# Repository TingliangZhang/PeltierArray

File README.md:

# PeltierArray
帕尔贴阵列 PCB and design

## 选型

MCU: Mega 2560 PRO (Embed) CH340G/ATmega2560-16AU

https://robotdyn.com/mega-2560-pro-embed-ch340g-atmega2560-16au.html

MOS管

[MOS(场效应管)/KIA50N03BD](https://item.szlcsc.com/458575.html)

接口

JST丨常用系列和型号选型推荐大全

https://www.szlcsc.com/info/13106.html

> 一开始选择 **PH系列 插座 1\*4P 间距2mm 卧插** B4B-PH-SM4-TB(LF)
>

后更改方案为

帕尔贴接口为PH2.0x2

PH-2A 2P 脚距2.0mm 直插

https://item.szlcsc.com/2693.html

温度传感器接口保持原来的

XH插座 1*2P 直针 间距2.5mm

https://item.szlcsc.com/169360.html

电源接口

> DC头：**DC连接器 DC-002-2.0A-1.3 DC插座 W11.4XD5.0XH7.4,内芯1.3,2A 12V**
>
> https://item.szlcsc.com/353351.html
>
> 可能要稍稍掰弯

更改为[AC/DC电源插座/DC-005 5.5-2.0MM 铁材质](https://item.szlcsc.com/16896.html)

发光二极管

LED灯绿_Iv=112-285_λd=520-535 二极管_发光二极管

SMT

或手贴

翠绿LED

https://item.szlcsc.com/207066.html

电容

[贴片电容/47uF(476) ±20% 25V](https://item.szlcsc.com/389810.html)

[引线型铝电解电容/47uF 50V黑高频](https://item.szlcsc.com/46672.html)

[贴片电容/10uF(106) ±20% 25V](https://item.szlcsc.com/97651.html)

其他

[肖特基二极管/SS14](https://item.szlcsc.com/2857.html)

[发光二极管/翠绿LED](https://item.szlcsc.com/207066.html)

半桥驱动

参考 [**wavgat**](https://wavgat.tmall.com/) 的MOS管驱动模块

https://detail.tmall.com/item.htm?id=599634712152

他上面用的MOS是[AOD4184A](https://item.szlcsc.com/100337.html)，N沟道

暂定选用[KIA50N03BD](https://item.szlcsc.com/458575.html)

封装为TO-252-2

## 3D MODEL

`.3dshapes`文件夹里面放`.step`和 `.wrl`模型文件，再在PCBNEW里面的元件封装属性里面选3D Setting添加3D Model，调整偏移对齐即可。

## Duplicate PCB sch and layout

参考

https://forum.kicad.info/t/how-to-duplicate-a-pcb-layout-in-kicad-5/12909

https://forum.kicad.info/t/replicate-layout-action-plugin/8539

https://github.com/MitjaNemec/Kicad_action_plugins

前提Hierarchical schematics：

https://docs.kicad-pcb.org/5.1/en/eeschema/eeschema.html#hierarchical-schematics

## 改为正反均要后需要用全桥

A5988:四路 DMOS 全桥式 PWM 电机驱动器

https://www.allegromicro.com/zh-CN/Products/Motor-Drivers/Brush-DC-Motor-Drivers/A5988

或者TB6612

https://toshiba.semicon-storage.com/us/semiconductor/product/motor-driver-ics/brushed-dc-motor-driver-ics/detail.TB6612FNG.html

或者DRV8833

https://www.ti.com/product/DRV8833

或者用以上两款电机驱动的Breakout Board，方便坏了的话更换。

或者参考Adafruit TB6612 1.2A DC/Stepper Motor Driver Breakout Board设计自己画

https://www.adafruit.com/product/2448

## 排针排母

TB6612 1x8排母

Mega Pro 2x3排母+2x16排母+2x21排母

只买2x20 2x3排母，剪一下

## TD1509配套电路

总体按照8V ~ 18V输入 5V 输出设计

SS52F肖特基二极管 20V 5A

https://item.szlcsc.com/328975.html

33uH 4.5A功率电感

https://item.szlcsc.com/160864.html

更便宜的选择：5A的33uH

https://item.szlcsc.com/338378.html

330uf/25V过孔电容

https://item.szlcsc.com/2403.html

## V2焊接过程中发现的问题

电感封装不对

TB6612引脚错误

没有开关（买个带开关的开关电源或者加一个12V回路功率开关）

指示灯，5V加LED+10k

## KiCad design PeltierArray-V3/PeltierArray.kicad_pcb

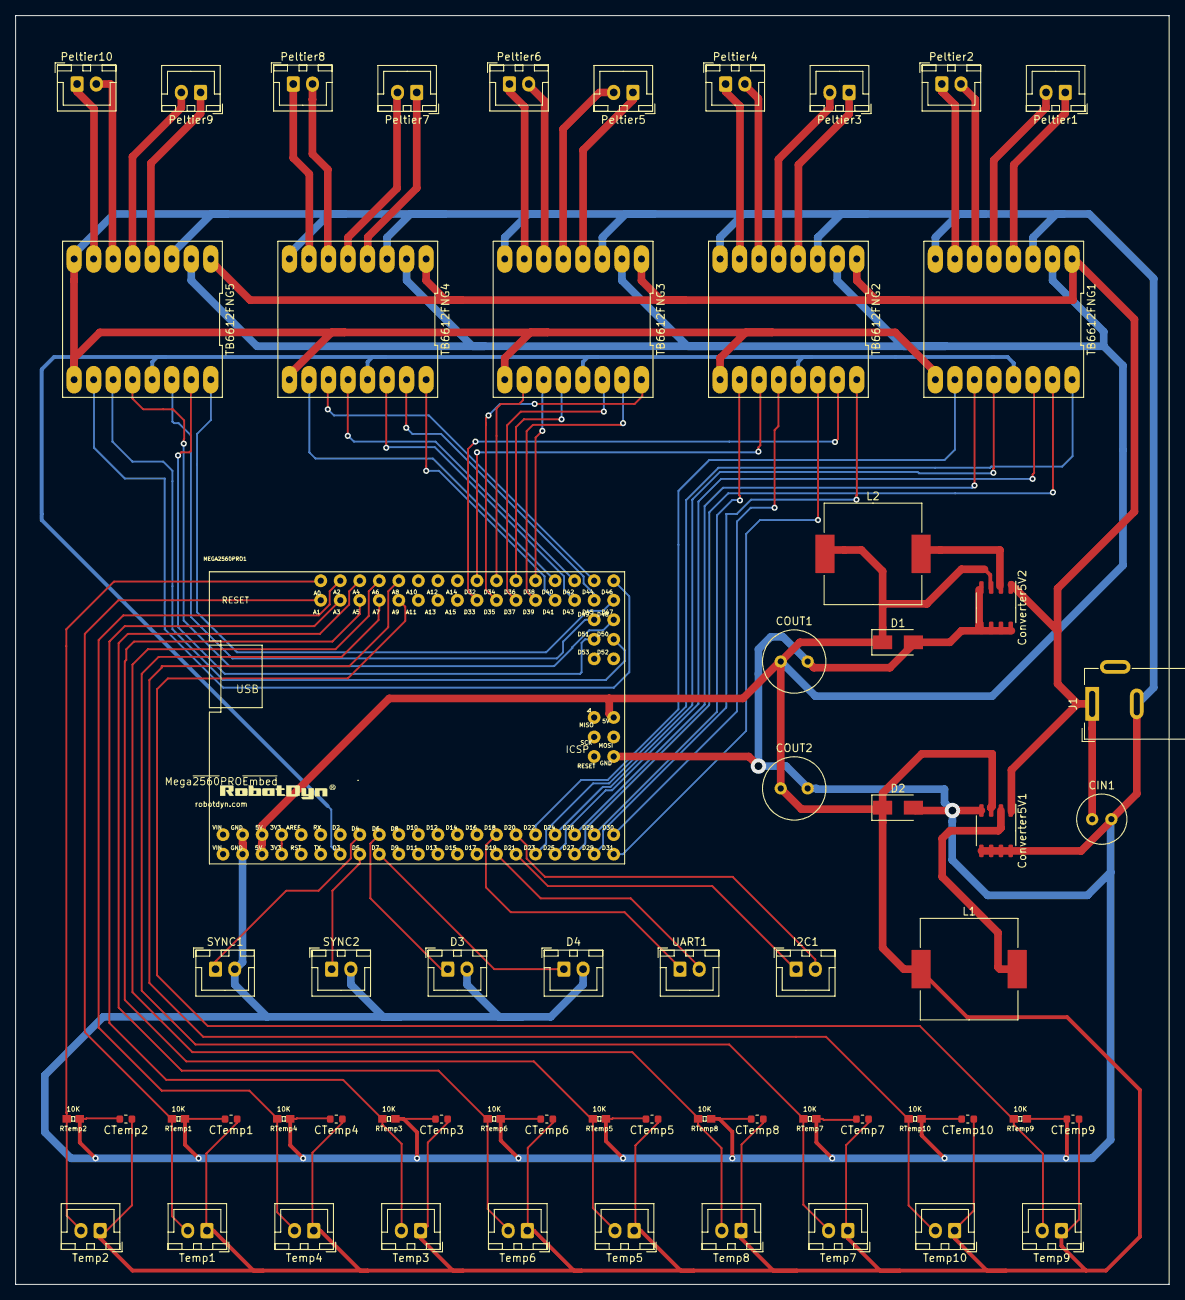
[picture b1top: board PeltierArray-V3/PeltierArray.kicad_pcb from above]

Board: 2 copper layers, 150.0 x 165.0 mm, 62 parts (0 on the bottom side), 75 nets.

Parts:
CIN1: CP47uF; C_Radial_D6.3mm_H11.0mm_P2.50mm
COUT1, COUT2: CP330uF25V; C_Radial_D8.0mm_H11.5mm_P3.50mm
CTemp1, CTemp2, CTemp3, CTemp4, CTemp5, CTemp6, CTemp7, CTemp8, CTemp9, CTemp10: 100nF; C_0603_1608Metric
Converter5V1, Converter5V2: TD1509; SOP-8_3.9x4.9mm_P1.27mm
D1, D2: D_Schottky; D_SMA
D3, D4: Conn_01x02_Male; JST_XH_B2B-XH-A_1x02_P2.50mm_Vertical
I2C1: Conn_01x02_Male; JST_XH_B2B-XH-A_1x02_P2.50mm_Vertical
J1: Barrel_Jack; BarrelJack_Wuerth_6941xx301002
L1, L2: L 33uF 4.5A; L_Wuerth_HCM-1390
MEGA2560PRO1: MEGA2560PRO-EMBED
Peltier1, Peltier2, Peltier3, Peltier4, Peltier5, Peltier6, Peltier7, Peltier8, Peltier9, Peltier10: Conn_01x02_Male; JST_XH_B2B-XH-A_1x02_P2.50mm_Vertical
RTemp1, RTemp2, RTemp3, RTemp4, RTemp5, RTemp6, RTemp7, RTemp8, RTemp9, RTemp10: 10K; 0603
SYNC1, SYNC2: Conn_01x02_Male; JST_XH_B2B-XH-A_1x02_P2.50mm_Vertical
TB6612FNG1, TB6612FNG2, TB6612FNG3, TB6612FNG4, TB6612FNG5: TB6612FNG; DIP-16_617_ELL
Temp1, Temp2, Temp3, Temp4, Temp5, Temp6, Temp7, Temp8, Temp9, Temp10: Conn_01x02_Male; JST_XH_B2B-XH-A_1x02_P2.50mm_Vertical
UART1: Conn_01x02_Male; JST_XH_B2B-XH-A_1x02_P2.50mm_Vertical

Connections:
+3V3: MEGA2560PRO1.3V3@1, MEGA2560PRO1.3V3@2
+5V: COUT1.1, COUT2.1, CTemp1.1, CTemp2.1, CTemp3.1, CTemp4.1, CTemp5.1, CTemp6.1, CTemp7.1, CTemp8.1, CTemp9.1, CTemp10.1, Converter5V1.3, Converter5V2.3, D1.1, D2.1, L1.1, L2.1, MEGA2560PRO1.5V@1, MEGA2560PRO1.5V@2, MEGA2560PRO1.5V@3, TB6612FNG1.2, TB6612FNG2.2, TB6612FNG3.2, TB6612FNG4.2, TB6612FNG5.2, Temp1.1, Temp2.1, Temp3.1, Temp4.1, Temp5.1, Temp6.1, Temp7.1, Temp8.1, Temp9.1, Temp10.1
+12V: CIN1.1, Converter5V1.1, Converter5V2.1, J1.1, TB6612FNG1.1, TB6612FNG2.1, TB6612FNG3.1, TB6612FNG4.1, TB6612FNG5.1
/A1: MEGA2560PRO1.D25, TB6612FNG1.14
/A2: MEGA2560PRO1.D24, TB6612FNG1.12
/A3: MEGA2560PRO1.D31, TB6612FNG2.14
/A4: MEGA2560PRO1.D30, TB6612FNG2.12
/A5: MEGA2560PRO1.D37, TB6612FNG3.14
/A6: MEGA2560PRO1.D36, TB6612FNG3.12
/A7: MEGA2560PRO1.D43, TB6612FNG4.14
/A8: MEGA2560PRO1.D42, TB6612FNG4.12
/A9: MEGA2560PRO1.D49, TB6612FNG5.14
/A10: MEGA2560PRO1.D48, TB6612FNG5.12
/B1: MEGA2560PRO1.D27, TB6612FNG1.15
/B2: MEGA2560PRO1.D26, TB6612FNG1.11
/B3: MEGA2560PRO1.D33, TB6612FNG2.15
/B4: MEGA2560PRO1.D32, TB6612FNG2.11
/B5: MEGA2560PRO1.D39, TB6612FNG3.15
/B6: MEGA2560PRO1.D38, TB6612FNG3.11
/B7: MEGA2560PRO1.D45, TB6612FNG4.15
/B8: MEGA2560PRO1.D44, TB6612FNG4.11
/B9: MEGA2560PRO1.D51, TB6612FNG5.15
/B10: MEGA2560PRO1.D50, TB6612FNG5.11
/D6: D3.1, MEGA2560PRO1.D6
/D7: D4.1, MEGA2560PRO1.D7
/PWM1: MEGA2560PRO1.D23, TB6612FNG1.16
/PWM2: MEGA2560PRO1.D22, TB6612FNG1.10
/PWM3: MEGA2560PRO1.D29, TB6612FNG2.16
/PWM4: MEGA2560PRO1.D28, TB6612FNG2.10
/PWM5: MEGA2560PRO1.D35, TB6612FNG3.16
/PWM6: MEGA2560PRO1.D34, TB6612FNG3.10
/PWM7: MEGA2560PRO1.D41, TB6612FNG4.16
/PWM8: MEGA2560PRO1.D40, TB6612FNG4.10
/PWM9: MEGA2560PRO1.D47, TB6612FNG5.16
/PWM10: MEGA2560PRO1.D46, TB6612FNG5.10
/RX1: MEGA2560PRO1.D19, UART1.2
/SCL: I2C1.1, MEGA2560PRO1.D21
/SDA: I2C1.2, MEGA2560PRO1.D20
/SYNC1: MEGA2560PRO1.D4, SYNC1.1
/SYNC2: MEGA2560PRO1.D5, SYNC2.1
/TX1: MEGA2560PRO1.D18, UART1.1
/Temp0: MEGA2560PRO1.A0, RTemp2.2, Temp2.2
/Temp1: MEGA2560PRO1.A1, RTemp1.2, Temp1.2
/Temp2: MEGA2560PRO1.A2, RTemp4.2, Temp4.2
/Temp3: MEGA2560PRO1.A3, RTemp3.2, Temp3.2
/Temp4: MEGA2560PRO1.A4, RTemp6.2, Temp6.2
/Temp5: MEGA2560PRO1.A5, RTemp5.2, Temp5.2
/Temp6: MEGA2560PRO1.A6, RTemp8.2, Temp8.2
/Temp7: MEGA2560PRO1.A7, RTemp7.2, Temp7.2
/Temp8: MEGA2560PRO1.A8, RTemp10.2, Temp10.2
/Temp9: MEGA2560PRO1.A9, RTemp9.2, Temp9.2
GND: CIN1.2, COUT1.2, COUT2.2, CTemp1.2, CTemp2.2, CTemp3.2, CTemp4.2, CTemp5.2, CTemp6.2, CTemp7.2, CTemp8.2, CTemp9.2, CTemp10.2, Converter5V1.4, Converter5V1.5, Converter5V1.6, Converter5V1.7, Converter5V1.8, Converter5V2.4, Converter5V2.5, Converter5V2.6, Converter5V2.7, Converter5V2.8, D1.2, D2.2, D3.2, D4.2, J1.2, MEGA2560PRO1.GND@1, MEGA2560PRO1.GND@2, MEGA2560PRO1.GND@3, RTemp1.1, RTemp2.1, RTemp3.1, RTemp4.1, RTemp5.1, RTemp6.1, RTemp7.1, RTemp8.1, RTemp9.1, RTemp10.1, SYNC1.2, SYNC2.2, TB6612FNG1.3, TB6612FNG1.8, TB6612FNG1.9, TB6612FNG2.3, TB6612FNG2.8, TB6612FNG2.9, TB6612FNG3.3, TB6612FNG3.8, TB6612FNG3.9, TB6612FNG4.3, TB6612FNG4.8, TB6612FNG4.9, TB6612FNG5.3, TB6612FNG5.8, TB6612FNG5.9
unnamed: Converter5V1.2, L1.2
unnamed: Converter5V2.2, L2.2
unnamed: Peltier1.1, TB6612FNG1.4
unnamed: Peltier1.2, TB6612FNG1.5
unnamed: Peltier2.1, TB6612FNG1.7
unnamed: Peltier2.2, TB6612FNG1.6
unnamed: Peltier3.1, TB6612FNG2.4
unnamed: Peltier3.2, TB6612FNG2.5
unnamed: Peltier4.1, TB6612FNG2.7
unnamed: Peltier4.2, TB6612FNG2.6
unnamed: Peltier5.1, TB6612FNG3.4
unnamed: Peltier5.2, TB6612FNG3.5
unnamed: Peltier6.1, TB6612FNG3.7
unnamed: Peltier6.2, TB6612FNG3.6
unnamed: Peltier7.1, TB6612FNG4.4
unnamed: Peltier7.2, TB6612FNG4.5
unnamed: Peltier8.1, TB6612FNG4.7
unnamed: Peltier8.2, TB6612FNG4.6
unnamed: Peltier9.1, TB6612FNG5.4
unnamed: Peltier9.2, TB6612FNG5.5
unnamed: Peltier10.1, TB6612FNG5.7
unnamed: Peltier10.2, TB6612FNG5.6
STBY: MEGA2560PRO1.D3, TB6612FNG1.13, TB6612FNG2.13, TB6612FNG3.13, TB6612FNG4.13, TB6612FNG5.13

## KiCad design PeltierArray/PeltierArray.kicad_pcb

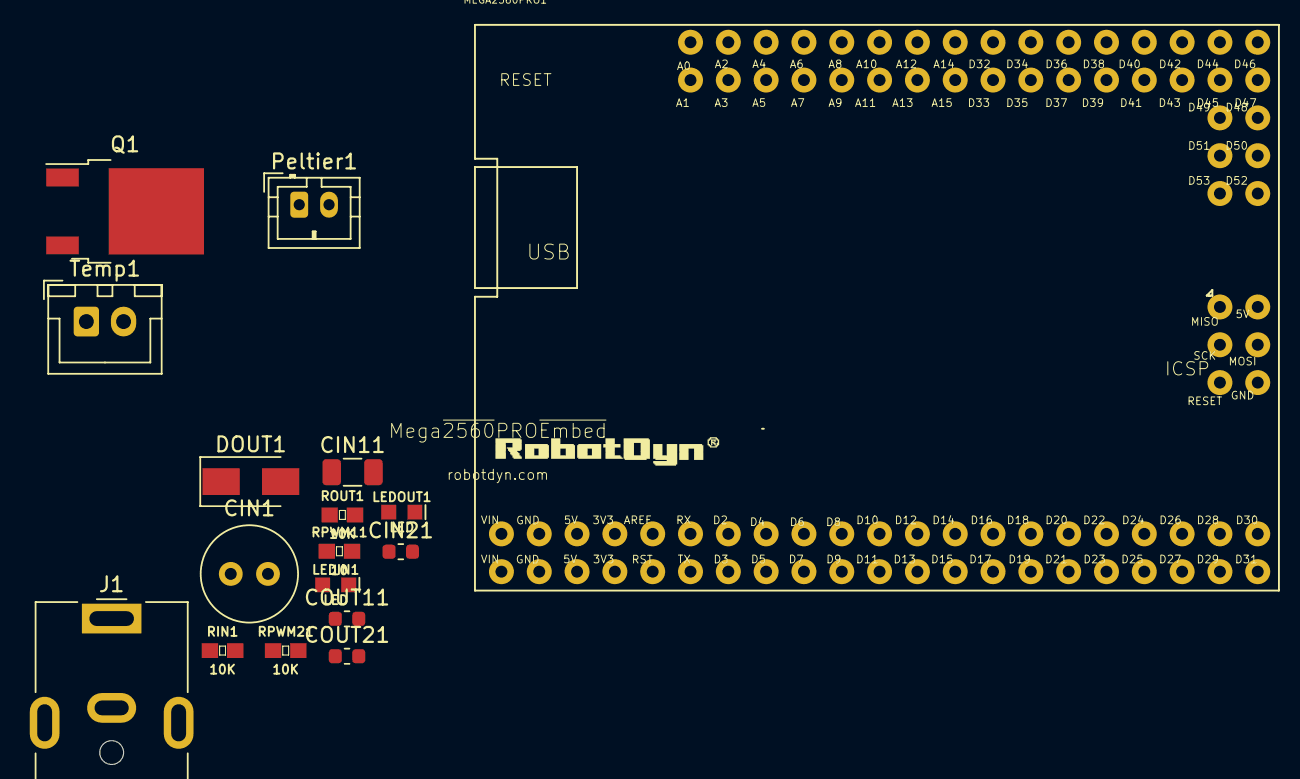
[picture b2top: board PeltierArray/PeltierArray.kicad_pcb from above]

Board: 2 copper layers, 17 parts (0 on the bottom side), 8 nets, no tracks yet.

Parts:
CIN1: CP47uF; C_Radial_D6.3mm_H11.0mm_P2.50mm
CIN11: 47uF; C_1206_3216Metric
CIN21: 1uF; C_0603_1608Metric
COUT11: 10uF; C_0603_1608Metric
COUT21: 1uF; C_0603_1608Metric
DOUT1: D; D_SMA
J1: Barrel_Jack; BarrelJack_CUI_PJ-063AH_Horizontal
LEDIN1: LED; LED-0603
LEDOUT1: LED; LED-0603
MEGA2560PRO1: MEGA2560PRO-EMBED
Peltier1: Conn_01x02_Male; JST_PH_B2B-PH-K_1x02_P2.00mm_Vertical
Q1: Q_NMOS_GDS; TO-252-2
RIN1: 10K; 0603
ROUT1: 10K; 0603
RPWM11: 10; 0603
RPWM21: 10K; 0603
Temp1: Conn_01x02_Male; JST_XH_B2B-XH-A_1x02_P2.50mm_Vertical

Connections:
+3V3: MEGA2560PRO1.3V3@1, MEGA2560PRO1.3V3@2
+5V: MEGA2560PRO1.5V@1, MEGA2560PRO1.5V@2, MEGA2560PRO1.5V@3
+12V: MEGA2560PRO1.VIN@1, MEGA2560PRO1.VIN@2
+BATT: CIN1.1, CIN11.1, CIN21.1, COUT11.1, COUT21.1, DOUT1.1, J1.1, Peltier1.1, RIN1.1, ROUT1.1
/PWM1: MEGA2560PRO1.D2, RPWM11.2, RPWM21.2
GND: CIN1.2, CIN11.2, CIN21.2, J1.2, J1.MP, MEGA2560PRO1.GND@1, MEGA2560PRO1.GND@2, MEGA2560PRO1.GND@3, Q1.3, RPWM21.1, Temp1.2
unnamed: COUT11.2, COUT21.2, DOUT1.2, Peltier1.2, Q1.2
unnamed: Q1.1, RPWM11.1

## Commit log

2020-10-08 IniWithMega2560Pro
2020-10-08 3DModel
2020-10-09 玉巨的MOS
2020-10-09 玉巨溜了
2020-10-09 Add Filter Temp Sensor
2020-10-09 热敏电阻
2020-10-09 del ignore
2020-10-10 Hierarchical schematics
2020-10-11 TB6612
2020-10-11 UART I2C
2020-10-12 BeginRoute
2020-10-12 FUUUUUUCK
2020-10-12 FinishRoute
2020-10-17 V3Begin
2020-10-17 V3Finish
2020-10-17 V3Print
2020-10-21 bomV3
2021-01-13 add lib
2021-02-04 Create sym-lib-table
